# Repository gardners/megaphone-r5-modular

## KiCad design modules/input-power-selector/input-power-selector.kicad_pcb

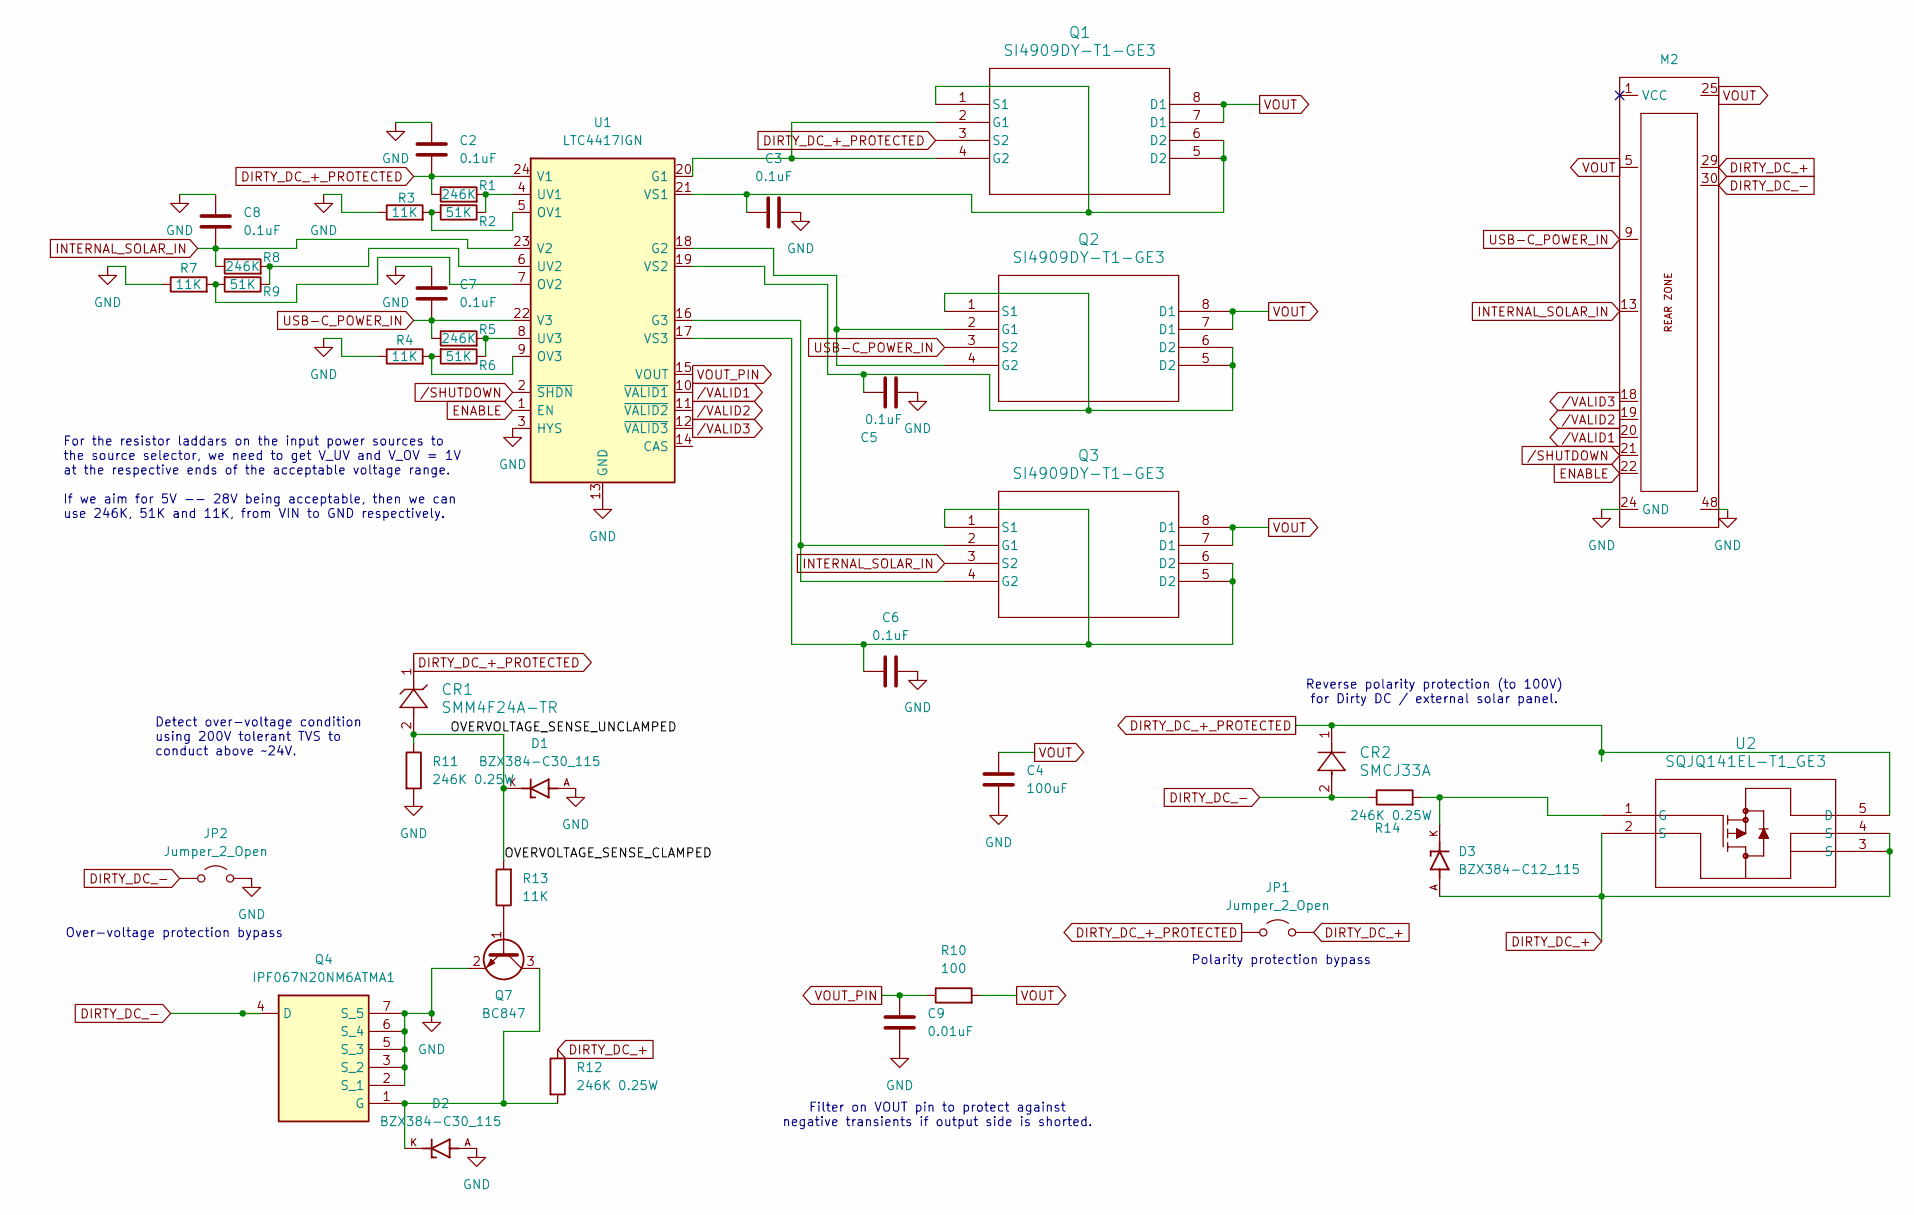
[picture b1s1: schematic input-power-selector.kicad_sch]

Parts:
C2, C3, C5, C6, C7, C8: 0.1uF; C_0805_2012Metric; Manufacturer_Part_Number 0805DC104MAT2A; Mouser Part Number 581-0805DC104MAT2A
C4: 100uF; C_0805_2012Metric
C9: 0.01uF; C_0805_2012Metric
CR1: SMM4F24A-TR; Manufacturer_Part_Number SMM4F24A-TR; Mouser Part Number 511-SMM4F24A-TR
CR2: SMCJ33A; Manufacturer_Part_Number 652-SMCJ33A; Mouser Part Number SMCJ33A
D1, D2: BZX384-C30_115; DIO_BZX384-C30_115; Manufacturer_Part_Number BZX384-C30,115; Mouser Part Number 771-BZX384-C30115
D3: BZX384-C12_115; DIO_BZX384-C30_115; Manufacturer_Part_Number BZX384-C12,115; Mouser Part Number 771-BZX384-C12115
JP1, JP2: Jumper_2_Open; SolderJumper-2_P1.3mm_Open_RoundedPad1.0x1.5mm
M2: MegaCastle2x24-Module-I47.0x56.2-M88887D8C0001-SPAREPAD
Q1, Q2, Q3: SI4909DY-T1-GE3; Manufacturer_Part_Number SI4909DY-T1-GE3; Mouser Part Number 78-SI4909DY-T1-GE3
Q4: IPF067N20NM6ATMA1; Mouser Part Number 726-IPF067N20NM6ATMA
Q7: BC847; SOT-23; Manufacturer_Part_Number 637-BC847B; Mouser Part Number BC847B
R1, R5, R8: 246K; R_0805_2012Metric
R2, R6, R9: 51K; R_0805_2012Metric; Manufacturer_Part_Number RV0805FR-0751KL; Mouser Part Number 603-RV0805FR-0751KL
R3, R4, R7, R13: 11K; R_0805_2012Metric; Manufacturer_Part_Number RT0805DRE0711KL; Mouser Part Number 603-RT0805DRE0711KL
R10: 100; R_0805_2012Metric; Manufacturer_Part_Number PCF0805R-100RBI; Mouser Part Number 756-PCF0805R100RBI
R11, R12, R14: 246K 0.25W; R_0805_2012Metric; Manufacturer_Part_Number PTN0805E2463BST1; Mouser Part Number 71-PTN0805E2463BST1
U1: LTC4417IGN; SSOP-24_3.9x8.7mm_P0.635mm; Manufacturer_Part_Number LTC4417IGN#PBF; Mouser Part Number 584-LTC4417IGN#PBF
U2: SQJQ141EL-T1_GE3; SOT95P280X120-6N; Manufacturer_Part_Number SQJQ141EL-T1_GE3; Mouser Part Number 78-SQJQ141EL-T1_GE3

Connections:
/OVERVOLTAGE_SENSE_CLAMPED: CR1.2, D1.K, R11.1, R13.2
DIRTY_DC_+: D3.A, JP1.2 (B), M2.29, R12.1, U2.2 (S), U2.3 (S), U2.4 (S)
DIRTY_DC_+_PROTECTED: C2.2, CR1.1, CR2.1, JP1.1 (A), Q1.3 (S2), R1.1, U1.24 (V1), U2.5 (D)
DIRTY_DC_-: CR2.2, JP2.1 (A), M2.30, Q4.4 (D), R14.1
ENABLE: M2.22, U1.1 (EN)
GND: C2.1, C3.2, C4.2, C5.2, C6.2, C7.1, C8.1, C9.2, D1.A, D2.A, JP2.2 (B), M2.24 (GND), M2.48, Q4.2 (S_1), Q4.3 (S_2), Q4.5 (S_3), Q4.6 (S_4), Q4.7 (S_5), Q7.2 (E), R3.1, R4.1, R7.1, R11.2, U1.3 (HYS), U1.13 (GND)
INTERNAL_SOLAR_IN: C8.2, M2.13, Q3.3 (S2), R8.1, U1.23 (V2)
unnamed: Q1.2 (G1), Q1.4 (G2), U1.20 (G1)
unnamed: C3.1, Q1.1 (S1), Q1.5 (D2), Q1.6 (D2), U1.21 (VS1)
unnamed: Q2.2 (G1), Q2.4 (G2), U1.18 (G2)
unnamed: C5.1, Q2.1 (S1), Q2.5 (D2), Q2.6 (D2), U1.19 (VS2)
unnamed: Q3.2 (G1), Q3.4 (G2), U1.16 (G3)
unnamed: C6.1, Q3.1 (S1), Q3.5 (D2), Q3.6 (D2), U1.17 (VS3)
unnamed: D2.K, Q4.1 (G), Q7.3 (C), R12.2
unnamed: Q7.1 (B), R13.1
unnamed: R2.2, R3.2, U1.5 (OV1)
unnamed: R7.2, R9.2, U1.7 (OV2)
unnamed: R4.2, R6.2, U1.9 (OV3)
unnamed: R1.2, R2.1, U1.4 (UV1)
unnamed: R8.2, R9.1, U1.6 (UV2)
unnamed: R5.2, R6.1, U1.8 (UV3)
unnamed: D3.K, R14.2, U2.1 (G)
USB-C_POWER_IN: C7.2, M2.9, Q2.3 (S2), R5.1, U1.22 (V3)
VOUT: C4.1, M2.5, M2.25, Q1.7 (D1), Q1.8 (D1), Q2.7 (D1), Q2.8 (D1), Q3.7 (D1), Q3.8 (D1), R10.2
VOUT_PIN: C9.1, R10.1, U1.15 (VOUT)
/SHUTDOWN: M2.21, U1.2 (~SHDN)
/VALID1: M2.20, U1.10 (~VALID1)
/VALID2: M2.19, U1.11 (~VALID2)
/VALID3: M2.18, U1.12 (~VALID3)

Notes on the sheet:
For the resistor laddars on the input power sources to the source selector, we need to get V_UV and V_OV = 1V at the respective ends of the acceptable voltage range. If we aim for 5V -- 28V being acceptable, then we can use 246K, 51K and 11K, from VIN to GND respectively.
Filter on VOUT pin to protect against negative transients if output side is shorted.
Reverse polarity protection (to 100V) for Dirty DC / external solar panel.
Over-voltage protection bypass
Detect over-voltage condition using 200V tolerant TVS to conduct above ~24V.
Polarity protection bypass

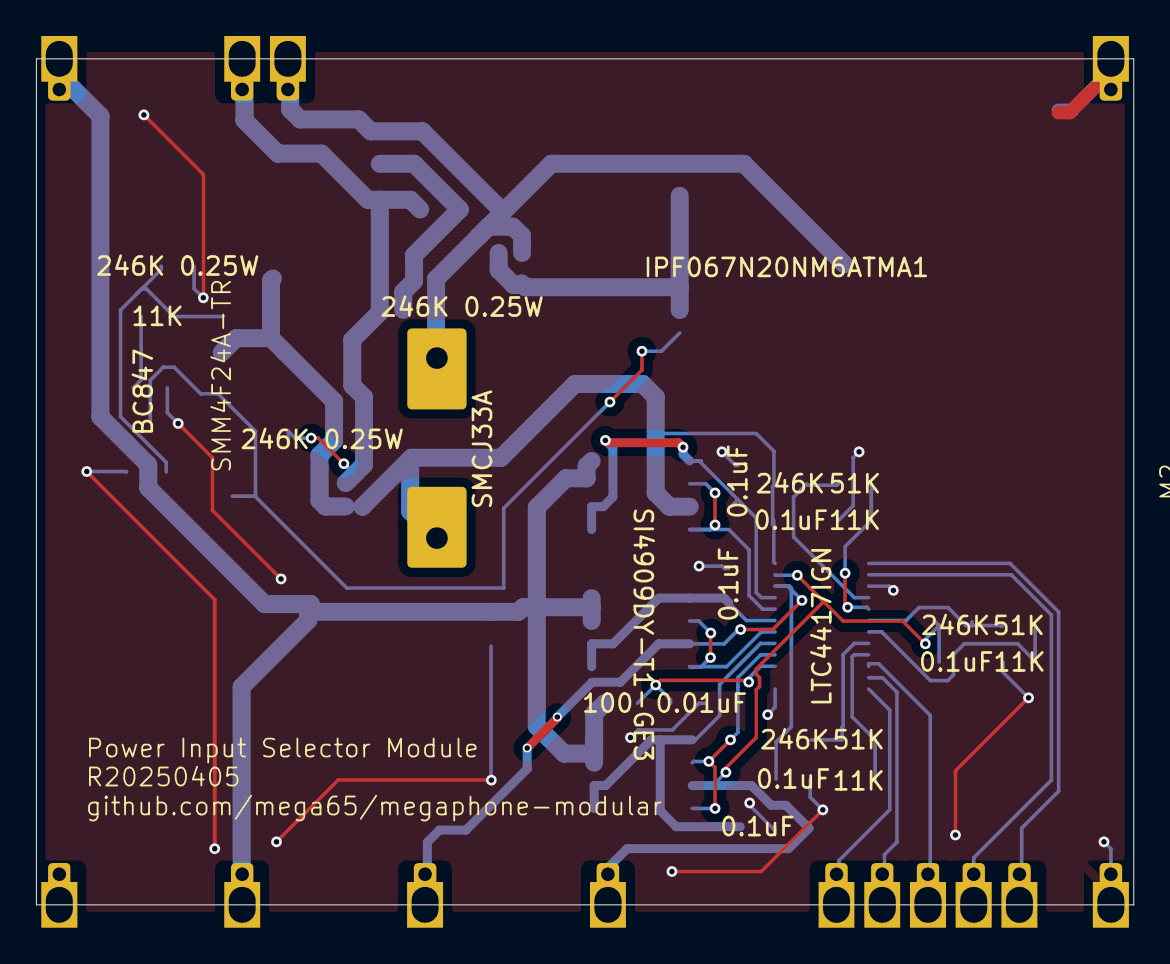
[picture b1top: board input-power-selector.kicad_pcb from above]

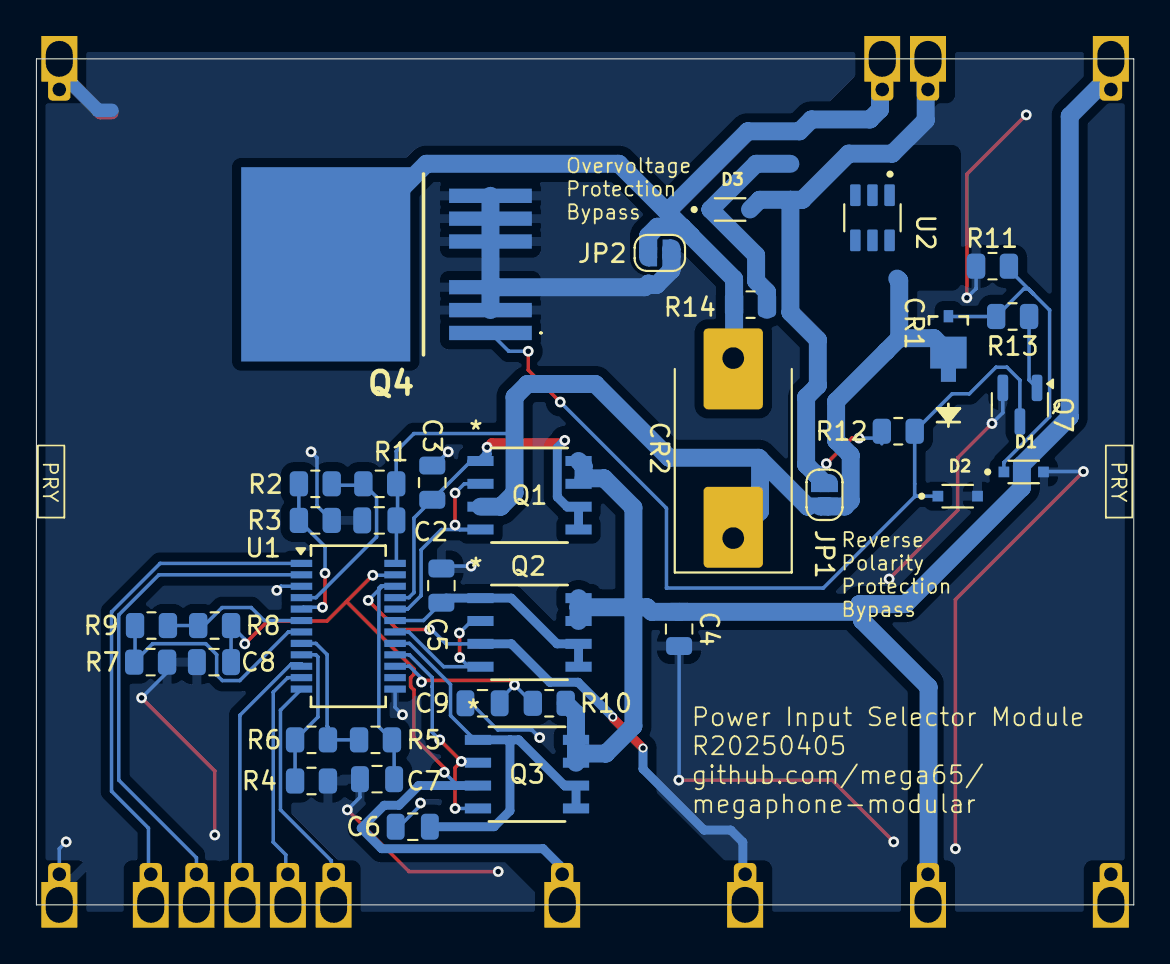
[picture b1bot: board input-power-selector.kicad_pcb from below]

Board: 2 copper layers, 61.0 x 47.0 mm, 37 parts (36 on the bottom side), 29 nets.

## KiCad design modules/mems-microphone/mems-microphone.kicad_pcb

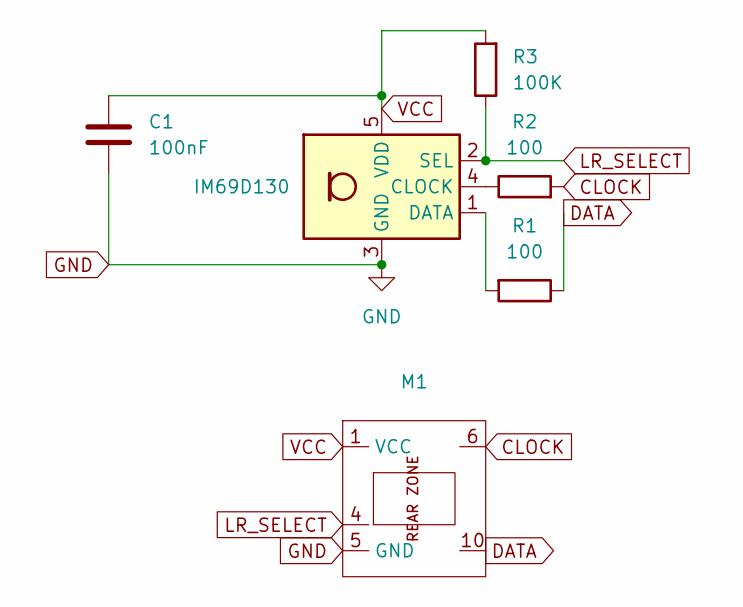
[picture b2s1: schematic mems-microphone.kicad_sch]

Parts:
C1: 100nF; C_1206_3216Metric; Mouser PN 581-12066D104KAT4A
M1: MegaCastle2x5-Module-I10.0x7.9-M9C4-SPAREPAD
MK1: IM69D130; Knowles_LGA-5_3.5x2.65mm; Mouser PN 726-IM69D130V01XTSA1
R1: 100; R_0603_1608Metric; Mfr. PN AC0603JR-07100RL; Mouser PN 603-AC0603JR-07100RL
R2: 100; R_0603_1608Metric; Mouser PN 603-AC0603JR-07100RL
R3: 100K; R_0603_1608Metric; Mouser PN 603-AC0603JR-07100KL

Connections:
CLOCK: M1.6, R2.2
DATA: M1.10, R1.1
GND: C1.2, M1.5 (GND), MK1.3 (GND)
LR_SELECT: M1.4, MK1.2 (SEL), R3.1
unnamed: MK1.4 (CLOCK), R2.1
unnamed: MK1.1 (DATA), R1.2
VCC: C1.1, M1.1 (VCC), MK1.5 (VDD), R3.2

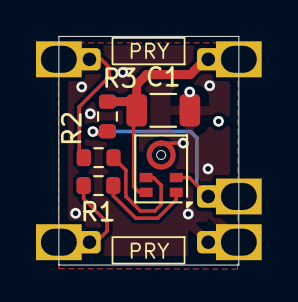
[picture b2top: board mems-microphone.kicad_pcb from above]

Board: 2 copper layers, 10.0 x 12.7 mm, 6 parts (1 on the bottom side), 7 nets.

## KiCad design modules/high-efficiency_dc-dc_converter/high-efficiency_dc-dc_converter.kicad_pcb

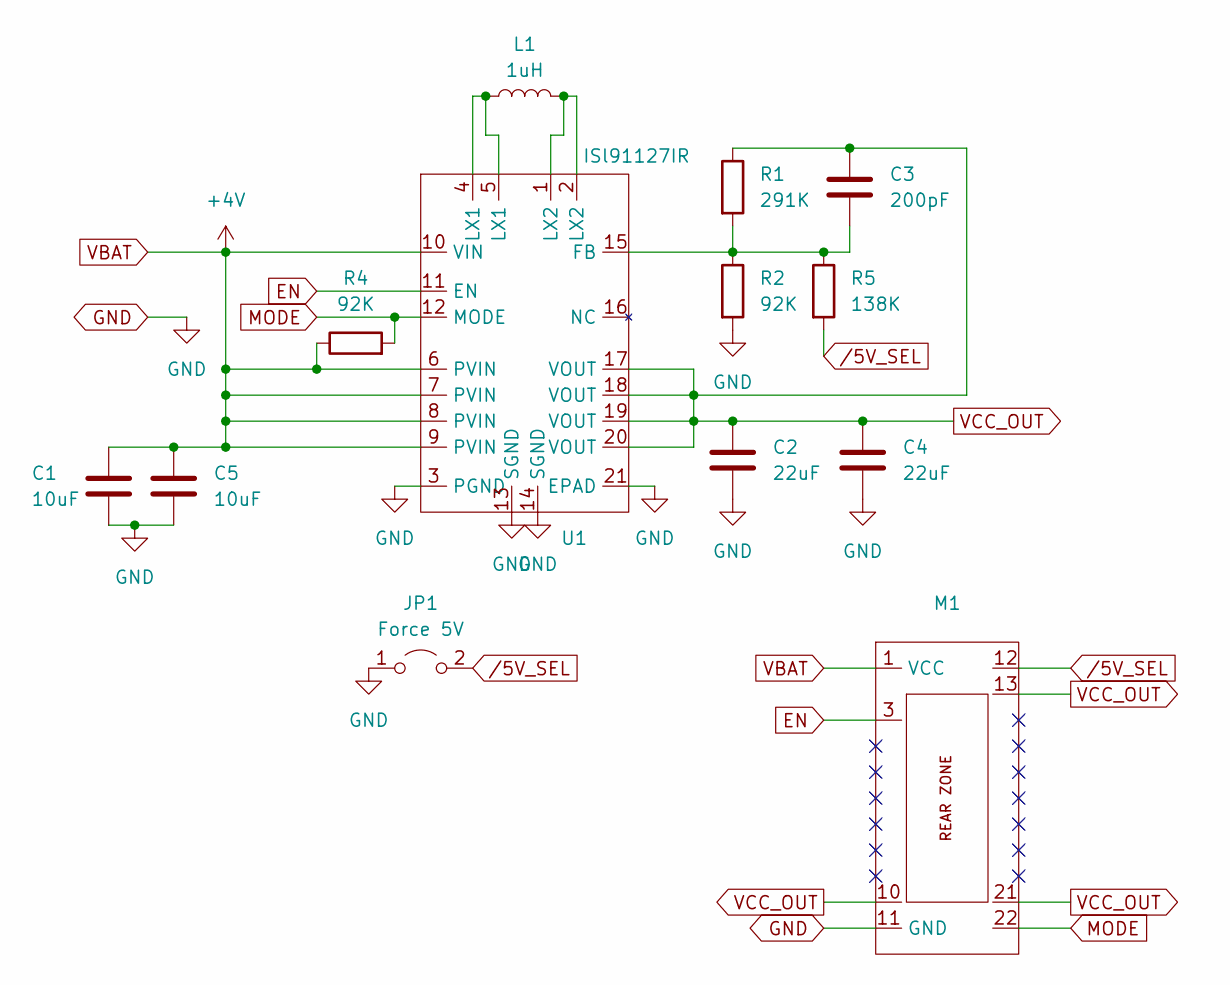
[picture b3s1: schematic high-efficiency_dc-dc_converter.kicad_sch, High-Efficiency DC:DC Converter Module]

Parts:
C1, C5: 10uF; C_0805_2012Metric
C2, C4: 22uF; C_0805_2012Metric
C3: 200pF; C_0805_2012Metric
JP1: Force 5V; SolderJumper-2_P1.3mm_Open_RoundedPad1.0x1.5mm
L1: 1uH; L_1008_2520Metric
M1: MegaCastle2x11-Module-I15.7x23.1-MA0780C-PANEL-NIBBLE
R1: 291K; R_0603_1608Metric
R2, R4: 92K; R_0603_1608Metric; Mouser PN 660-RN73H1JTD9202B25
R5: 138K; R_0603_1608Metric
U1: ISl91127IR; QFN50P400X400X90-21N; Mouser PN 968-ISL91127IRAZ-T

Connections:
EN: M1.3, U1.11 (EN)
GND: C1.2, C2.2, C4.2, C5.2, JP1.1 (A), M1.11 (GND), R2.2, U1.3 (PGND), U1.13 (SGND), U1.14 (SGND), U1.21 (EPAD)
MODE: M1.22, R4.2, U1.12 (MODE)
unnamed: L1.1, U1.4 (LX1), U1.5 (LX1)
unnamed: L1.2, U1.1 (LX2), U1.2 (LX2)
unnamed: C3.2, R1.2, R2.1, R5.1, U1.15 (FB)
VBAT: C1.1, C5.1, M1.1 (VCC), R4.1, U1.6 (PVIN), U1.7 (PVIN), U1.8 (PVIN), U1.9 (PVIN), U1.10 (VIN)
VCC_OUT: C2.1, C3.1, C4.1, M1.10, M1.13, M1.21, R1.1, U1.17 (VOUT), U1.18 (VOUT), U1.19 (VOUT), U1.20 (VOUT)
/5V_SEL: JP1.2 (B), M1.12, R5.2

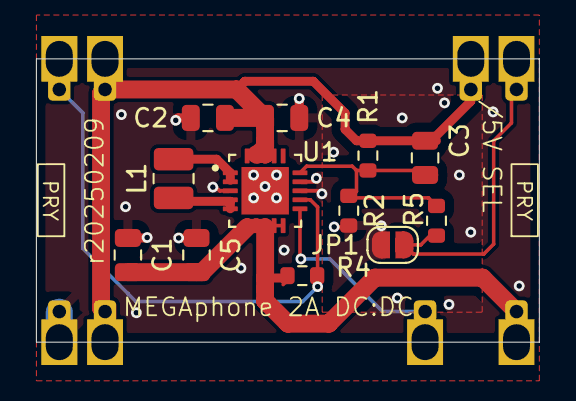
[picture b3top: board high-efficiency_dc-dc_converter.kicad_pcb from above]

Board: 2 copper layers, 27.9 x 15.7 mm, 13 parts (1 on the bottom side), 9 nets.

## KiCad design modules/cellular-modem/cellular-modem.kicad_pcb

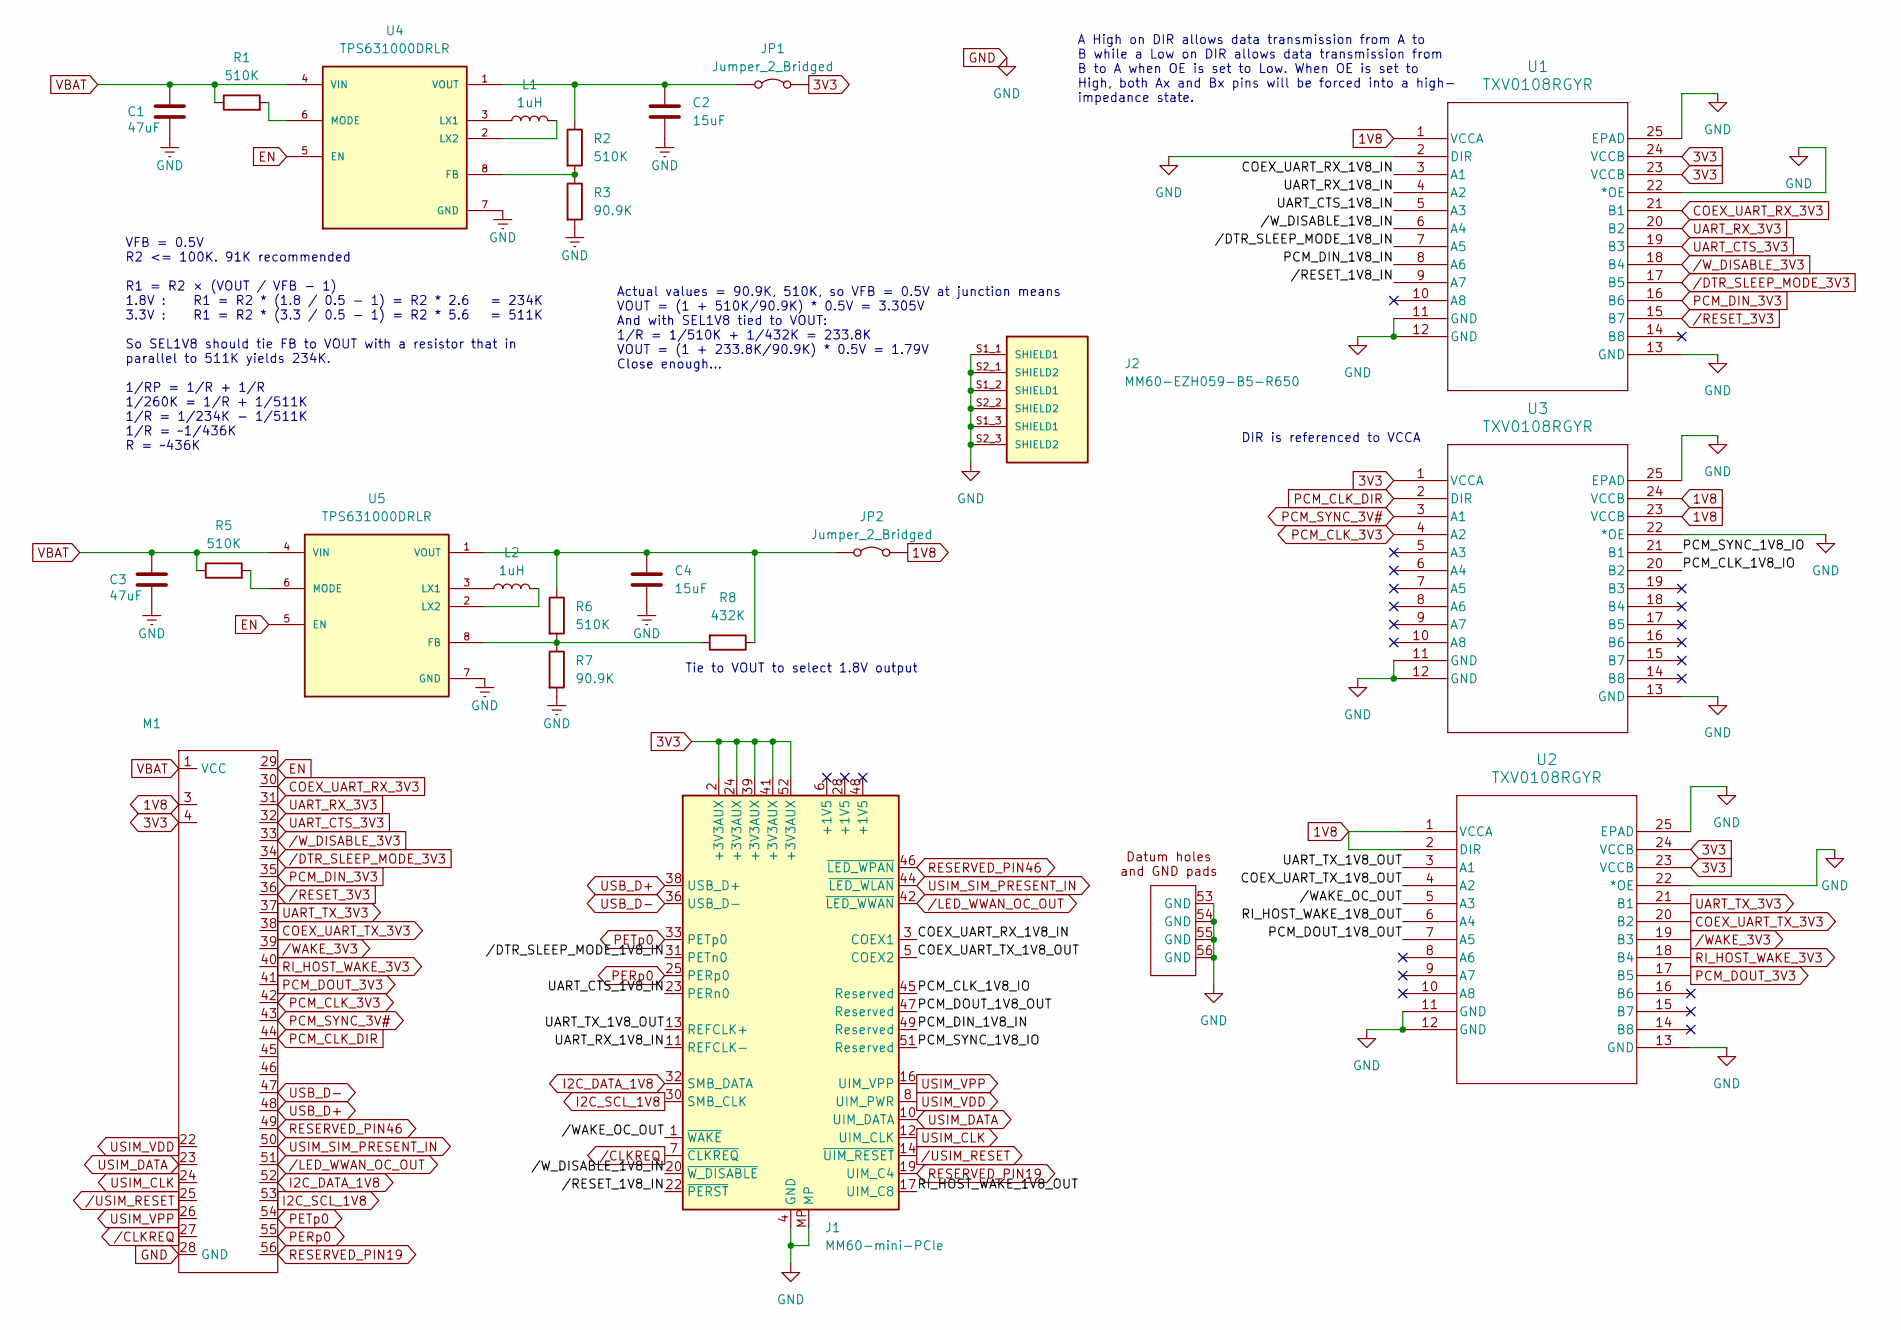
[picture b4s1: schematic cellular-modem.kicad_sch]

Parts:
C1: 47uF; C_0805_2012Metric; Mouser_PN GRM219R60J476ME44
C2, C4: 15uF; C_0805_2012Metric; Mfr. PN C2012X7S1A156M125AC; Mouser_PN 810-C2012X7S1A156M1C
C3: 47uF; C_0805_2012Metric; Mfr. PN GRM219R60J476ME44D; Mouser_PN GRM219R60J476ME44
J1: MM60-mini-PCIe; CONN_MM60-52B1-E1-R650_JAE; Mfr. PN MM60-52B1-G1-R850; Mouser_PN 656-MM6052B1G1R850
J2: MM60-EZH059-B5-R650; JAE_MM60-EZH059-B5-R650; PARTREV 3; Mouser_PN 656-MM60-EZH059-B5-R
JP1, JP2: Jumper_2_Bridged; SolderJumper-2_P1.3mm_Bridged2Bar_RoundedPad1.0x1.5mm
L1: 1uH; L_1008_2520Metric_Pad1.43x2.20mm_HandSolder; Mouser_PN 81-DFE252012P-1R0MP2
L2: 1uH; L_1008_2520Metric_Pad1.43x2.20mm_HandSolder; Mfr. PN DFE252012P-1R0M=P2; Mouser_PN 81-DFE252012P-1R0MP2
M1: MegaCastle2x28-Module-I42.8x66.3-MB00007FFFFFFFF-SPAREPAD
R1, R2, R5, R6: 510K; R_0805_2012Metric; Mouser_PN CR0805-JW-514ELF
R3, R7: 90.9K; R_0805_2012Metric; Mfr. PN RE0805FRE0790K9L; Mouser_PN 603-RE0805FRE0790K9L
R8: 432K; R_0805_2012Metric; Mfr. PN RC0805FR-07432KL; Mouser_PN 603-RC0805FR-07432KL
U1, U2, U3: TXV0108RGYR; VQFN24_RGY_TEX; Mfr. PN TXV0108RGYR; Mouser_PN 595-TXV0108RGYR
U4, U5: TPS631000DRLR; SOT50P160X60-8N; PARTREV B; Mouser_PN 595-TPS631000DRLR

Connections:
1V8: JP2.2 (B), M1.3, U1.1 (VCCA), U2.1 (VCCA), U2.2 (DIR), U3.23 (VCCB), U3.24 (VCCB)
3V3: J1.2 (+3V3AUX), J1.24 (+3V3AUX), J1.39 (+3V3AUX), J1.41 (+3V3AUX), J1.52 (+3V3AUX), JP1.2 (B), M1.4, U1.23 (VCCB), U1.24 (VCCB), U2.23 (VCCB), U2.24 (VCCB), U3.1 (VCCA)
/COEX_UART_RX_1V8_IN: J1.3 (COEX1), U1.3 (A1)
/COEX_UART_TX_1V8_OUT: J1.5 (COEX2), U2.4 (A2)
/PCM_CLK_1V8_IO: J1.45 (Reserved), U3.20 (B2)
/PCM_DIN_1V8_IN: J1.49 (Reserved), U1.8 (A6)
/PCM_DOUT_1V8_OUT: J1.47 (Reserved), U2.7 (A5)
/PCM_SYNC_1V8_IO: J1.51 (Reserved), U3.21 (B1)
/RI_HOST_WAKE_1V8_OUT: J1.17 (UIM_C8), U2.6 (A4)
/UART_CTS_1V8_IN: J1.23 (PERn0), U1.5 (A3)
/UART_RX_1V8_IN: J1.11 (REFCLK-), U1.4 (A2)
/UART_TX_1V8_OUT: J1.13 (REFCLK+), U2.3 (A1)
//DTR_SLEEP_MODE_1V8_IN: J1.31 (PETn0), U1.7 (A5)
//RESET_1V8_IN: J1.22 (~PERST), U1.9 (A7)
//WAKE_OC_OUT: J1.1 (~WAKE), U2.5 (A3)
//W_DISABLE_1V8_IN: J1.20 (~W_DISABLE), U1.6 (A4)
COEX_UART_RX_3V3: M1.30, U1.21 (B1)
COEX_UART_TX_3V3: M1.38, U2.20 (B2)
EN: M1.29, U4.5 (EN), U5.5 (EN)
GND: C1.1, C2.2, C3.1, C4.2, J1.4 (GND), J1.9 (GND), J1.15 (GND), J1.18 (GND), J1.21 (GND), J1.26 (GND), J1.27 (GND), J1.29 (GND), J1.34 (GND), J1.35 (GND), J1.37 (GND), J1.40 (GND), J1.43 (GND), J1.50 (GND), J1.53 (GND), J1.54 (GND), J1.55 (GND), J1.56 (GND), J1.MP, J2.S1_1 (SHIELD1), J2.S1_2 (SHIELD1), J2.S1_3 (SHIELD1), J2.S2_1 (SHIELD2), J2.S2_2 (SHIELD2), J2.S2_3 (SHIELD2), M1.28 (GND), R3.2, R7.2, U1.2 (DIR), U1.11 (GND), U1.12 (GND), U1.13 (GND), U1.22 (*OE), U1.25 (EPAD), U2.11 (GND), U2.12 (GND), U2.13 (GND), U2.22 (*OE), U2.25 (EPAD), U3.11 (GND), U3.12 (GND), U3.13 (GND), U3.22 (*OE), U3.25 (EPAD), U4.7 (GND), U5.7 (GND)
I2C_DATA_1V8: J1.32 (SMB_DATA), M1.52
I2C_SCL_1V8: J1.30 (SMB_CLK), M1.53
unnamed: C2.1, JP1.1 (A), R2.1, U4.1 (VOUT)
unnamed: C4.1, JP2.1 (A), R6.1, R8.1, U5.1 (VOUT)
unnamed: R2.2, R3.1, U4.8 (FB)
unnamed: L1.1, U4.3 (LX1)
unnamed: L1.2, U4.2 (LX2)
unnamed: R1.2, U4.6 (MODE)
unnamed: R6.2, R7.1, R8.2, U5.8 (FB)
unnamed: L2.1, U5.3 (LX1)
unnamed: L2.2, U5.2 (LX2)
unnamed: R5.2, U5.6 (MODE)
PCM_CLK_3V3: M1.42, U3.4 (A2)
PCM_CLK_DIR: M1.44, U3.2 (DIR)
PCM_DIN_3V3: M1.35, U1.16 (B6)
PCM_DOUT_3V3: M1.41, U2.17 (B5)
PCM_SYNC_3V#: M1.43, U3.3 (A1)
PERp0: J1.25 (PERp0), M1.55
PETp0: J1.33 (PETp0), M1.54
RESERVED_PIN19: J1.19 (UIM_C4), M1.56
RESERVED_PIN46: J1.46 (~LED_WPAN), M1.49
RI_HOST_WAKE_3V3: M1.40, U2.18 (B4)
UART_CTS_3V3: M1.32, U1.19 (B3)
UART_RX_3V3: M1.31, U1.20 (B2)
UART_TX_3V3: M1.37, U2.21 (B1)
USB_D+: J1.38 (USB_D+), M1.48
USB_D-: J1.36 (USB_D-), M1.47
USIM_CLK: J1.12 (UIM_CLK), M1.24
USIM_DATA: J1.10 (UIM_DATA), M1.23
USIM_SIM_PRESENT_IN: J1.44 (~LED_WLAN), M1.50
USIM_VDD: J1.8 (UIM_PWR), M1.22
USIM_VPP: J1.16 (UIM_VPP), M1.26
VBAT: C1.2, C3.2, M1.1 (VCC), R1.1, R5.1, U4.4 (VIN), U5.4 (VIN)
/CLKREQ: J1.7 (~CLKREQ), M1.27
/DTR_SLEEP_MODE_3V3: M1.34, U1.17 (B5)
/LED_WWAN_OC_OUT: J1.42 (~LED_WWAN), M1.51
/RESET_3V3: M1.36, U1.15 (B7)
/USIM_RESET: J1.14 (~UIM_RESET), M1.25
/WAKE_3V3: M1.39, U2.19 (B3)
/W_DISABLE_3V3: M1.33, U1.18 (B4)

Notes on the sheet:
Tie to VOUT to select 1.8V output
Actual values = 90.9K, 510K, so VFB = 0.5V at junction means VOUT = (1 + 510K/90.9K) * 0.5V = 3.305V And with SEL1V8 tied to VOUT: 1/R = 1/510K + 1/432K = 233.8K VOUT = (1 + 233.8K/90.9K) * 0.5V = 1.79V Close enough...
VFB = 0.5V R2 <= 100K. 91K recommended R1 = R2 × (VOUT / VFB - 1) 1.8V : R1 = R2 * (1.8 / 0.5 - 1) = R2 * 2.6 = 234K 3.3V : R1 = R2 * (3.3 / 0.5 - 1) = R2 * 5.6 = 511K So SEL1V8 should tie FB to VOUT with a resistor that in parallel to 511K yields 234K. 1/RP = 1/R + 1/R 1/260K = 1/R + 1/511K 1/R = 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
DIR is referenced to VCCA
A High on DIR allows data transmission from A to B while a Low on DIR allows data transmission from B to A when OE is set to Low. When OE is set to High, both Ax and Bx pins will be forced into a high- impedance state.

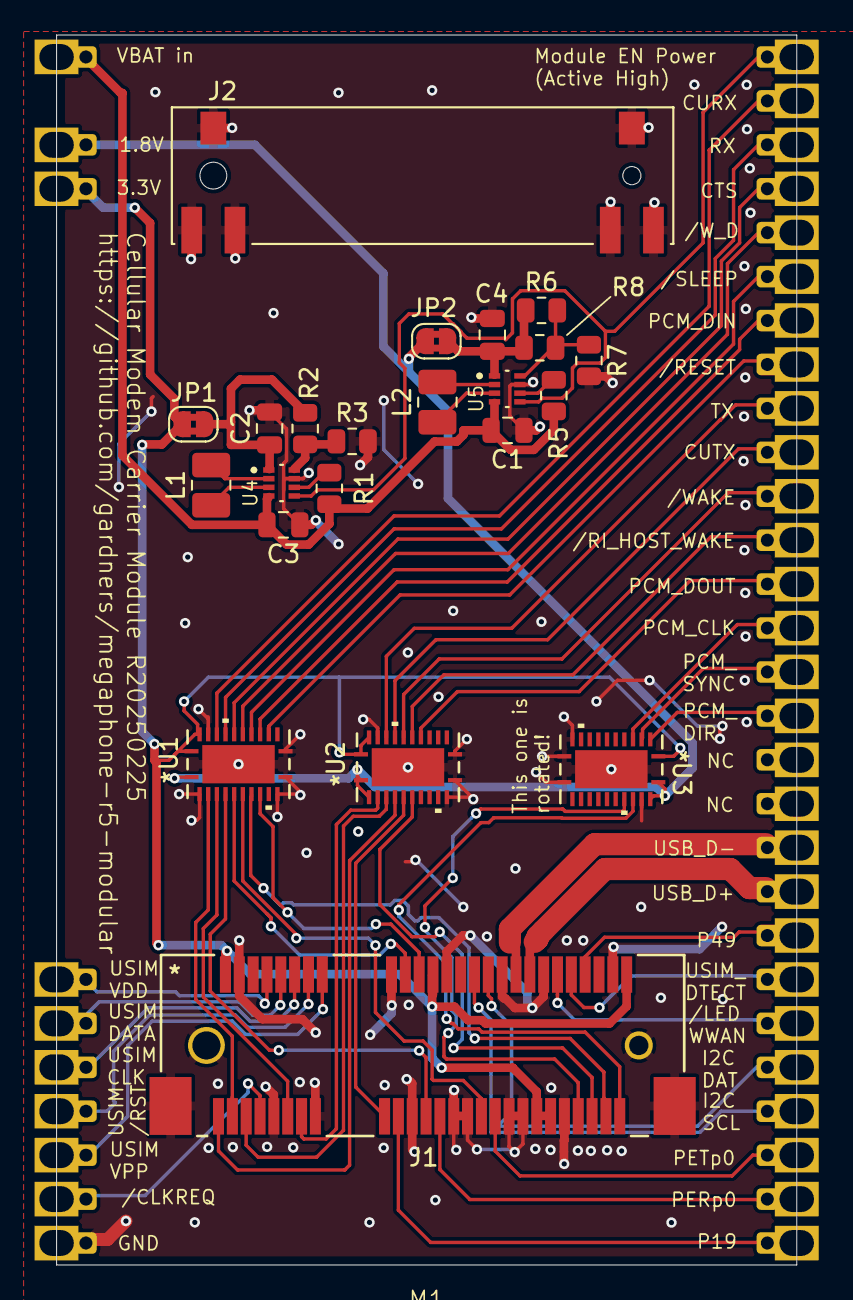
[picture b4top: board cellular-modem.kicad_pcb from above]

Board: 4 copper layers, 42.8 x 71.1 mm, 23 parts (0 on the bottom side), 60 nets.

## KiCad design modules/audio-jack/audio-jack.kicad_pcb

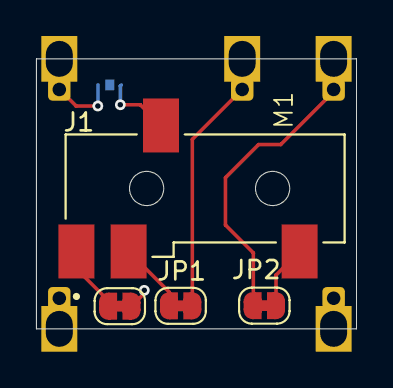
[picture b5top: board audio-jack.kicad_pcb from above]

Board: 2 copper layers, 17.8 x 15.0 mm, 6 parts (1 on the bottom side), 8 nets.

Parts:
J1: SJ-43514-SMT-TR; CUI_SJ-43514-SMT-TR
JP1, JP2, JP3, JP4: Jumper_2_Bridged; SolderJumper-2_P1.3mm_Bridged_RoundedPad1.0x1.5mm
M1: MegaCastle2x7-Module-I15.0x13.0-M8314-SPAREPAD

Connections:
GND: JP3.2 (B), M1.7 (GND)
LEFT: JP4.1 (A), M1.8
MIC: JP1.2 (B), M1.12
unnamed: J1.4, JP1.1 (A)
unnamed: J1.2, JP2.2 (B)
unnamed: J1.1, JP3.1 (A)
unnamed: J1.3, JP4.2 (B)
RIGHT: JP2.1 (A), M1.14

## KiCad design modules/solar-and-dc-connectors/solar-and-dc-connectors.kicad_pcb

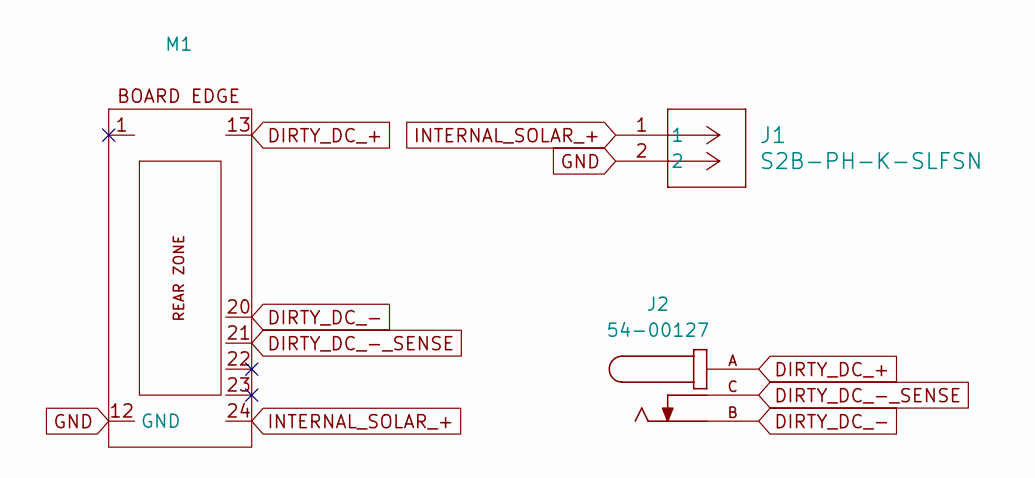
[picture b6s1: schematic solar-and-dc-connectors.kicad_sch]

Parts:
J1: S2B-PH-K-SLFSN; CONN_S2B-PH-K-S_JST; Mouser PN 306-S2BPHKSLFSNPP
J2: 54-00127; TENSILITY_54-00127; PARTREV A
M1: MegaCastle2x12-Module-I20.0x25.7-M80181F-SPAREPAD

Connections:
DIRTY_DC_+: J2.A, M1.13
DIRTY_DC_-: J2.B, M1.20
DIRTY_DC_-_SENSE: J2.C, M1.21
GND: J1.2, M1.12 (GND)
INTERNAL_SOLAR_+: J1.1, M1.24

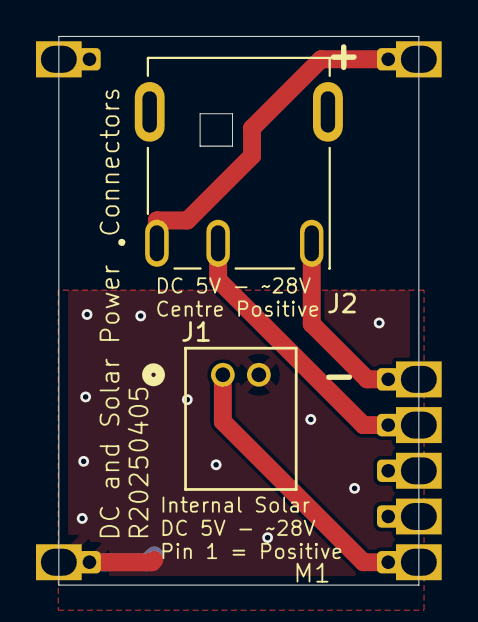
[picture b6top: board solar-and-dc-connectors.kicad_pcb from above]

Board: 2 copper layers, 20.0 x 30.5 mm, 3 parts (0 on the bottom side), 5 nets.

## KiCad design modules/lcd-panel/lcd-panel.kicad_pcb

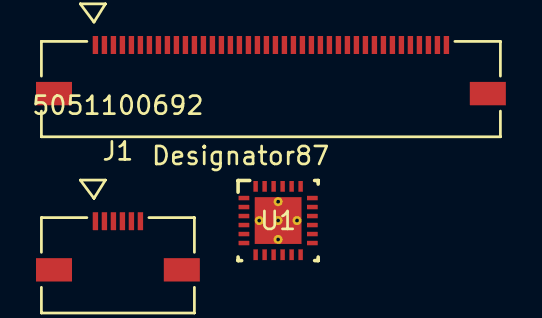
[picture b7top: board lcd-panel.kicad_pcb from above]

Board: 2 copper layers, 3 parts (0 on the bottom side), 4 nets, no tracks yet.

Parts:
J1: 5051100692; CON_5051100692_MOL
J2: 5051104091; CON_5051104091_MOL
U1: LP8556SQ-E09/NOPB; RTW0024A

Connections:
GND: J1.P1, J1.P2, J2.3, J2.29, J2.36, J2.P1, J2.P2, U1.3 (GND_SW), U1.4 (GND_SW), U1.10 (GND), U1.11 (GND), U1.15 (GND), U1.21 (FSET), U1.24 (GND), U1.25 (GND)
LEDA: J2.2, U1.20 (VBOOST)
LEDK: J2.1, U1.12 (LED1)
unnamed: U1.1 (SW), U1.2 (SW)

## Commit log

2025-02-25 finish SD and SIM card holder footprint and symbol
2025-02-28 reverse text direction for part labels on DC:DC
2025-02-28 exported gerbers for SIM SD card module
2025-03-01 add footprints for USB-C power in
2025-03-01 begin working on usb-c power in module
2025-03-01 finish usb-c power in module and generate gerbers
2025-03-01 add footprints for MOSFETs for input power selecter
2025-03-01 begin work on input power selecter
2025-03-01 begin laying out DC input selector
2025-03-01 add symbols and footprints for input power selector components
2025-03-01 more input power selector footprints
2025-03-01 add models for N-channel MOSFET
2025-03-01 add more footprints etc
2025-03-01 finish laying out schematic for power selector input protection
2025-03-02 add models for simple Zener diode
2025-03-02 prepare for pcb layout for power selector
2025-03-04 add footprints for SMCJ28A. work on reverse polarity protection
2025-03-04 work on laying out power input selector
2025-03-04 more layout fixing on power selector
2025-03-04 add models etc for more components
2025-03-04 add missing 3D model
2025-03-04 update input source selecter PCB layout
2025-03-04 add module outline for input source selecter
2025-03-04 fix remaining important DRC violations
2025-03-05 add symbols for 2-pin internal solar panel
2025-03-05 add footprints for DC barrel jack
2025-03-05 begin working on solar and DC power input module
2025-03-05 add footprints for battery screw terminal
2025-03-05 add missing footprints and symbols
2025-03-05 begin work on battery connector module
2025-03-05 add footprint for battery power connector module
2025-03-05 work on battery connector module
2025-03-05 finish battery connector module design
2025-04-25 work towards parsing properties in symbols
2025-04-25 quote requirements text
2025-04-25 begin making library to track parts
2025-04-25 add links to requirements table
2025-04-25 fix property parsing
2025-04-25 work on bomtool schematic parser
2025-04-25 update mppt charger submodule
2025-04-25 ignore power symbols
2025-04-25 fix symbol property parsing
2025-04-25 update module requirements summary
2025-04-25 rename and move module requirements reporting page
2025-04-25 rework property parser. Still broken, though.
2025-04-25 add renamed file
2025-04-25 make CSV file actually be CSV
2025-04-25 fix requirement numbering transposition
2025-04-25 begin adding markdown table showing requirements mapping for each module
2025-04-25 add header to requirements table
2025-04-25 fix compiler warnings
2025-04-25 reduce debug output
2025-04-25 update module requirements mapping table
2025-04-25 fix bm83 uart rx framing
2025-04-25 more work on lcd panel module
2025-04-25 more work on oauth and digikey search
2025-04-25 get digikey search initially working
2025-04-25 work towards automatic digikey parts search
2025-04-25 update footprints file
2025-04-25 update bluetooth module
2025-04-25 begin work on bluetooth module
2025-04-25 work towards auto-fetching digikey parts
2025-04-25 update offset of spare hole for pads
2025-04-25 begin work on lcd panel modeul
2025-04-25 fix compiler warning and catch file creation errors
2025-04-25 downgrade requirement 2.1.2 to desirable
2025-04-25 more work on bt monitor test program
2025-04-25 begin searching for parts in library
2025-04-25 get oauth working, but flow is still broken
2025-04-25 add footprints for BM83
2025-04-25 add footprints etc for LCD cable connectors
2025-04-25 fix parsing out of digikey parts
2025-04-25 work on parser for BM83 UART packets
2025-04-25 add code to read and write parts library
2025-04-25 first cut at adding "backup vias" for footprints
2025-04-25 sparepad now a footpring option
2025-04-25 fix sparepad footprint problems
2025-04-25 use rounded rect for spare pads
2025-04-25 fix typo in footprint-gen.c
2025-06-13 Adding Mouser parts to power selector
2025-06-13 Updating high-efficiency_dc-dc_converter
2025-06-13 KiCad v9 adding new footprints
2025-06-13 Updating solar-and-dc
2025-06-13 Updating cellular modem - adding KiCad git ignore
2025-06-13 Adding more mouser parts to schematics
2025-06-13 Updating PART NOs
2025-06-13 Adding cellular modem footprints
2025-06-13 stop munging module size
2025-06-13 Updating mems mic
2025-06-13 use much more efficient combination selection algorithm.
2025-06-13 fix pin numbers and shape for right half
2025-06-13 Updating parts
2025-06-13 Adding Mouser parts to sc
2025-06-13 Removing not needed lck files
2025-06-13 add mega65-libc as sub-module for telephony software
2025-06-13 more work on OTF to bitmap font converter
2025-06-13 add mega65-libc to .gitmodules
2025-06-13 begin writing tool to convert OTF to megaphone fonts
2025-06-13 Update bluetooth
2025-06-13 Updating footprint on input power selector
2025-06-13 update LCD module
2025-06-13 update mppt-charge-controller
2025-06-13 Updating USB-Power-IN
2025-06-13 get phone font rendering nicely
2025-06-13 build test program for shres
2025-06-14 implement iterating over whole font
2025-06-14 begin generating FCM pixel data for fonts
2025-06-14 begin working on test program for unicode font handling
2025-06-14 successfully cat text file from shared resource area
2025-06-14 update mega65-libc for SHRES API implementation
2025-06-14 use shopen() to cat text file
2025-06-14 implement creating MEGA65 pre-rendered fonts
2025-06-14 use shseek() in dummy test
2025-06-14 add note for downloading Noto emoji and text fonts
2025-06-14 add symlinks to pick out TTFs from Noto font archive
2025-06-14 write script to put shared resources on SD card
2025-06-14 begin working on actual unicode display via SHRES fonts
2025-06-14 work on MEGAphone screen setup
2025-06-14 begin implementing glyph cache
2025-06-15 implement colour cube setup functions
2025-06-15 setup 332 colour cube on start
2025-06-15 add generator for attribute tables
2025-06-15 implement writing to screen and colour RAM
2025-06-15 try to draw an "A"
2025-06-15 fix screen setup bugs
2025-06-15 fix some draw_glyph bugs
2025-06-15 enable alpha compositor. debug glyph display problems
2025-06-15 progress towards unicode glyph rendering
2025-06-15 progress towards properly rendering interlaced FCM unicode glyphs
2025-06-16 update mega65-libc to get fixed shread()
2025-06-16 swap nybl packing order and card order
2025-06-16 fix glyph render height to actually fit in 16px
2025-06-16 begin adding support for rendering coloured emoji
2025-06-16 add script to convert twitter emojis
2025-06-16 correctly select alt palette
2025-06-16 enable VIC-III attrs to allow alternate palette selection
2025-06-16 work around first row of text top pixel glitch
2025-06-16 update unicode font test program
2025-06-22 more work on UTF-8 Unicode string printer
2025-06-22 begin implementing printing Unicode strings
2025-06-22 begin work on UTF-8 parsing
2025-06-22 begin working on text box rendering stuff
2025-07-18 begin implementing d81 manipulation code
2025-07-19 more work on telephony provisioning utility
2025-07-19 get provision to compile under linux
2025-07-19 more work towards phone provisioning utility
2025-07-19 fix fseek() arg order. Get provision writing full structure
2025-07-28 fix bugs in D81 formatting
2025-07-28 create other disk images for phone
2025-07-28 fix sector links in 2nd logical sectors
2025-07-28 add code to test sector ordering
